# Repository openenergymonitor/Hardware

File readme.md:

## OpenEnergyMonitor Hardware

OpenEnergyMonitor hardware is open source hardware. This github repository hosts all the Eagle schematic and board files for the hardware units in addition to images for quick access.

**Update: most hardware designs have now been moved to dedicated repos, see individual folders**

### EmonTx

- [emonTx SMT V3](emonTxV3) - Latest generation of the emonTx Arduino compatible low power wireless energy monitoring node
- [emonTx Through-hole V2](emonTxV2) - A low-power wireless energy-monitoring node - Arduino compatible

### EmonTx Shield

- [emonTx Shield SMT](emontx-shield-smt) - An Arduino compatible energy monitoring shield
- [emonTx Shield Through-hole](emontx-shield-v1) - A wireless energy monitoring Arduino compatible shield

### EmonTH

- [emonTH](emonTH) - Temperature and humidity monitoring node

### EmonGLCD

- [emonGLCD](emonGLCD_V1) - Wireless open-source graphical LCD display unit - Arduino compatible

### RF12Pi Adapter Board

- [RF12Pi Adapter Board](RFM2Pi/readme.md)

### Development

- [12 Input Pulse Counter](12-input-pulse-counter) - Design in development for a 12-input puse counter for interfacing with 12 utility meters. 12 Input Pulse counter development notes and documentation can be found on the main OpenEnergyMonitor site [here](http://openenergymonitor.org/emon/buildingblocks/12-input-pulse-counting)

- [In-line energy monitor + Relay unit](relay-unit/readme.md)

### Open Hardware

Hardware designs (schematics and CAD) files are licensed under the [Creative Commons Attribution-ShareAlike 3.0 Unported License](http://creativecommons.org/licenses/by-sa/3.0/) and follow the terms of the [OSHW (Open-source hardware) Statement of Principles 1.0.](http://freedomdefined.org/OSHW)

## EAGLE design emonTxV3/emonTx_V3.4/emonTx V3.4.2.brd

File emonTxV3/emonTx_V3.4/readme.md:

## Moved to https://github.com/openenergymonitor/emontx3

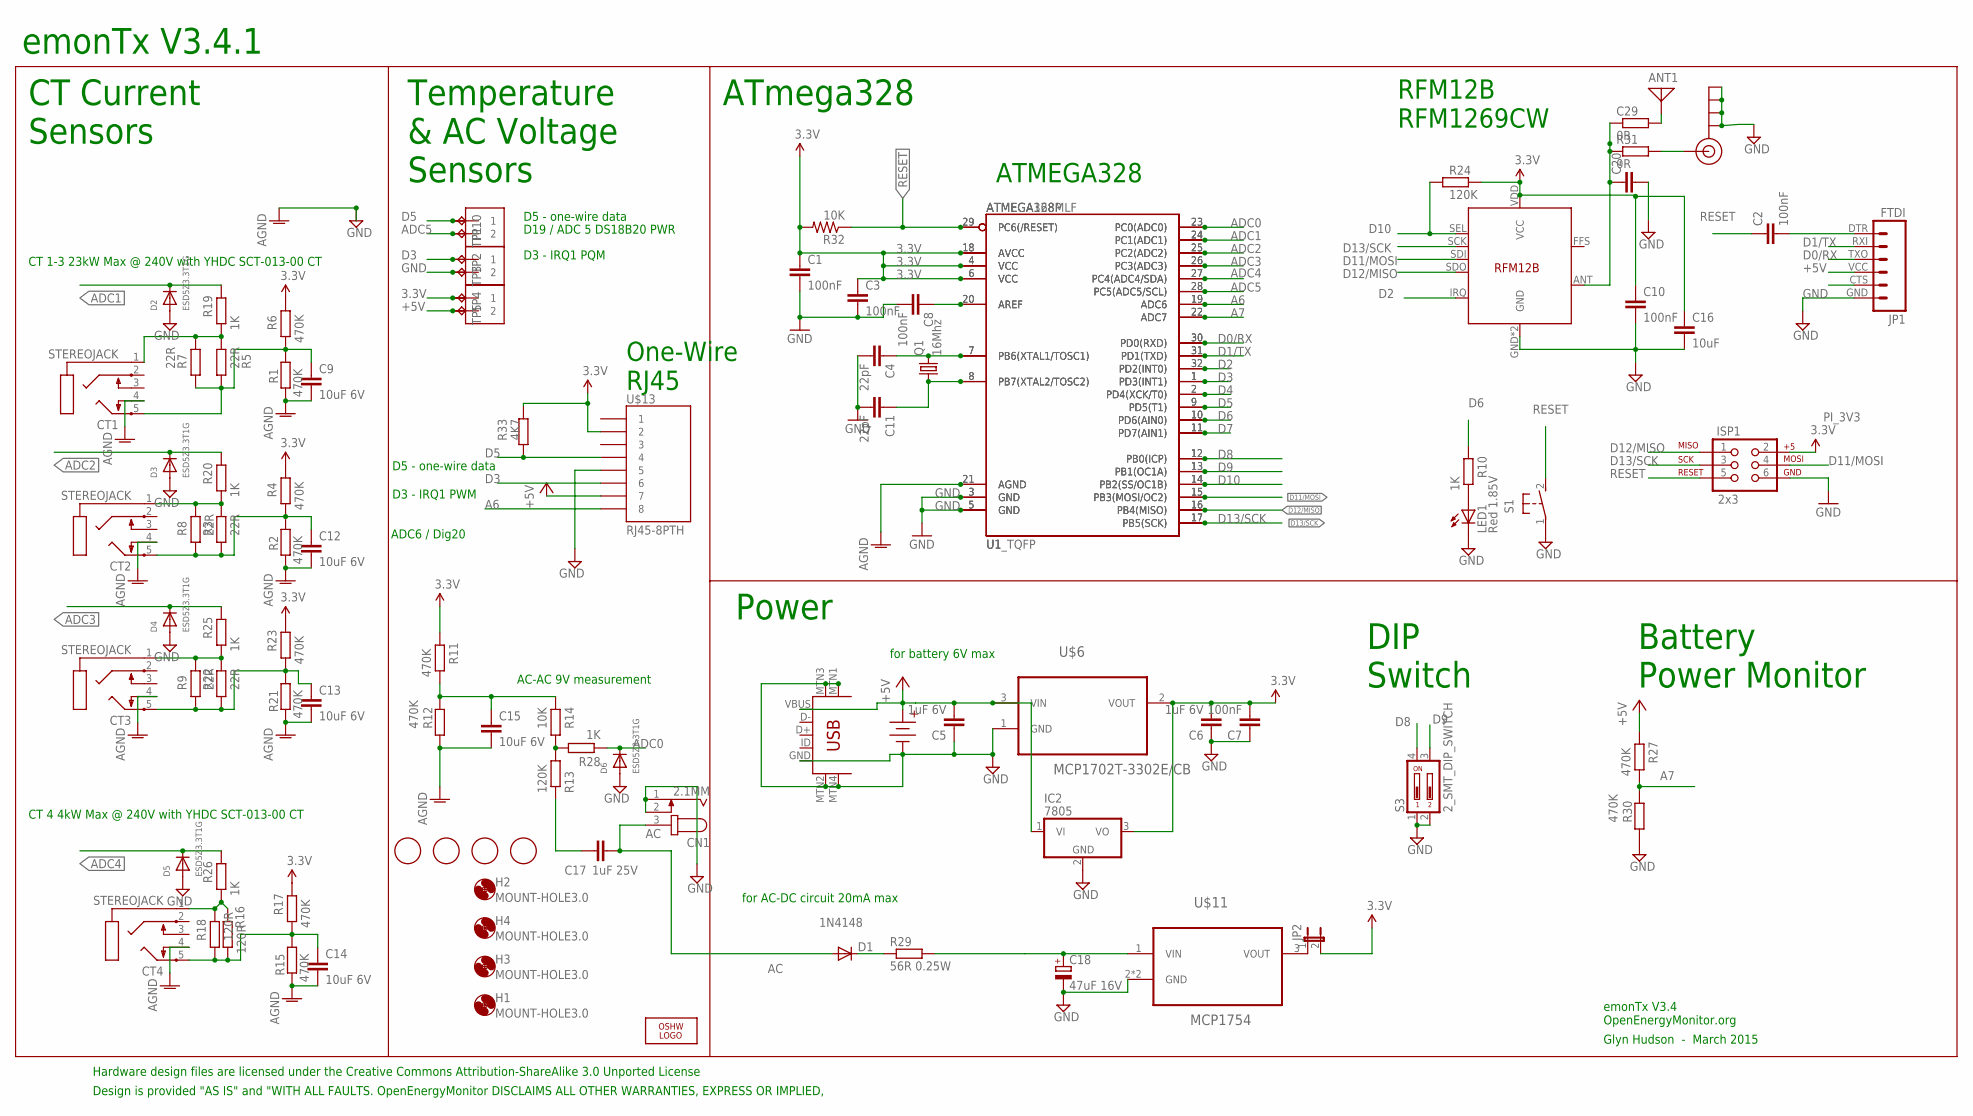
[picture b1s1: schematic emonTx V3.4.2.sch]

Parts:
ANT1: ANTENNA; PAD-01
C1, C2, C3, C7, C8, C10: 100nF; C0603
C4, C11: 22pF; C0603
C5, C6: 1uF 6V; C0603
C9, C12, C13, C14, C15: 10uF 6V; C0603
C16: 10uF; C0603
C17: 1uF 25V; C0603
C18: 47uF 16V; PANASONIC_D
C20: ant tune?; C0603
C29: 0R; R0603
CN1: 2.1MM; SPC4077
CT1, CT2, CT3, CT4: STEREOJACK; STX3100
D1: 1N4148; SOD-323
D2, D3, D4, D5, D6: ESD5Z3.3T1G; SOD-523
H1, H2, H3, H4: MOUNT-HOLE3.0; 3,0
IC2: 7805; TO220V
ISP1: 2x3; 2X3
J3, J5, J6: 1X2-3.5MM
J$1: SMA_EDGE; SMA-EDGE
JP1: FTDI; FTDI_BASIC
JP2: JUMPER-2PTH_LOCK; 1X02_LOCK
LED1: Red 1.85V; CHIP-LED0805
LOGO1: OSHW_LOGO_6MILX0200-NT; OSHW_6X200_NOTEXT
Q1: 16Mhz; HC49UP
R1, R2, R4, R6, R11, R12, R15, R17, R21, R23, R27, R30: 470K; R0603
R3, R5, R22: 22R; 0204/7
R7, R8, R9: 22R; R1206
R10, R19, R20, R25, R26, R28: 1K; R0603
R13, R24: 120K; R0603
R14, R32: 10K; R0603
R16: 120R; 0204/7
R18: 120R; R1206
R29: 56R 0.25W; R1206
R31: 0R; R0603
R33: 4K7; R0603
S1: 31-XX; B3F-31XX
S3: 2_SMT_DIP_SWITCH; DIP_SWITCH_SMT
TP1, TP2, TP3, TP4, TP5, TP10: TPPAD1-13; P1-13
U1: ATMEGA168MLF; MLF32
U1_TQFP: ATMEGA328P; TQFP32-08
U$1, U$4, U$5, U$7: FIDUCIAL; FIDUCIAL_1MM
U$3: 4.5V; AAA_PCB_HOLDER
U$6: MCP1702T-3302E/CB; SOT95P237X112-3N
U$10: USB-MINIB-5PIN; USB-MINIB-CISECO
U$11: MCP1754; SOT89
U$13: RJ45-8PTH; RJ45-8
U$14: RFM12B

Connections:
3.3V: C1.1, C3.1, C6.2, C7.2, C10.1, C16.1, IC2.3 (VO), ISP1.2, J6.1, JP2.2, R4.2, R6.2, R11.2, R17.2, R23.2, R24.2, R32.2, R33.1, TP4.TP, U1.4 (VCC), U1.6 (VCC), U1.18 (AVCC), U1_TQFP.4 (VCC), U1_TQFP.6 (VCC), U1_TQFP.18 (AVCC), U$6.2 (VOUT), U$13.2, U$14.VDD (VCC)
+5V: C5.2, IC2.1 (VI), J6.2, JP1.VCC (4), R27.2, TP5.TP, U$3.+, U$6.3 (VIN), U$10.VBUS, U$13.7
A6: U1.19 (ADC6), U1_TQFP.19 (ADC6), U$13.8
A7: R27.1, R30.2, U1.22 (ADC7), U1_TQFP.22 (ADC7)
AC: C17.2, CN1.3, D1.2 (A)
ADC0: D6.K (C), R28.1, U1.23 (PC0(ADC0)), U1_TQFP.23 (PC0(ADC0))
ADC1: D2.K (C), R19.2, U1.24 (PC1(ADC1)), U1_TQFP.24 (PC1(ADC1))
ADC2: D3.K (C), R20.2, U1.25 (PC2(ADC2)), U1_TQFP.25 (PC2(ADC2))
ADC3: D4.K (C), R25.2, U1.26 (PC3(ADC3)), U1_TQFP.26 (PC3(ADC3))
ADC4: D5.K (C), R26.2, U1.27 (PC4(ADC4/SDA)), U1_TQFP.27 (PC4(ADC4/SDA))
ADC5: J3.2, TP1.TP, U1.28 (PC5(ADC5/SCL)), U1_TQFP.28 (PC5(ADC5/SCL))
AGND: C9.2, C12.2, C13.2, C14.2, C15.2, CT1.4, CT2.4, CT3.4, CT4.4, R1.2, R2.2, R12.1, R15.2, R21.2, U1.21 (AGND), U1_TQFP.21 (AGND)
D0/RX: JP1.TXO (3), U1.30 (PD0(RXD)), U1_TQFP.30 (PD0(RXD))
D1/TX: JP1.RXI (2), U1.31 (PD1(TXD)), U1_TQFP.31 (PD1(TXD))
D2: U1.32 (PD2(INT0)), U1_TQFP.32 (PD2(INT0)), U$14.IRQ
D3: J5.1, TP2.TP, U1.1 (PD3(INT1)), U1_TQFP.1 (PD3(INT1)), U$13.6
D4: U1.2 (PD4(XCK/T0)), U1_TQFP.2 (PD4(XCK/T0))
D5: J3.1, R33.2, TP10.TP, U1.9 (PD5(T1)), U1_TQFP.9 (PD5(T1)), U$13.4
D6: R10.2, U1.10 (PD6(AIN0)), U1_TQFP.10 (PD6(AIN0))
D7: U1.11 (PD7(AIN1)), U1_TQFP.11 (PD7(AIN1))
D8: S3.4, U1.12 (PB0(ICP)), U1_TQFP.12 (PB0(ICP))
D9: S3.3, U1.13 (PB1(OC1A)), U1_TQFP.13 (PB1(OC1A))
D10: R24.1, U1.14 (PB2(SS/OC1B)), U1_TQFP.14 (PB2(SS/OC1B)), U$14.SEL
D11/MOSI: ISP1.4, U1.15 (PB3(MOSI/OC2)), U1_TQFP.15 (PB3(MOSI/OC2)), U$14.SDI
D12/MISO: ISP1.1, U1.16 (PB4(MISO)), U1_TQFP.16 (PB4(MISO)), U$14.SDO
D13/SCK: ISP1.3, U1.17 (PB5(SCK)), U1_TQFP.17 (PB5(SCK)), U$14.SCK
DIG1: C20.1, C29.1, R31.1, U$14.ANT
GND: C1.2, C3.2, C4.2, C5.1, C6.1, C7.1, C8.2, C10.2, C11.2, C16.2, C18.-, C20.2, CN1.1, CN1.2, D2.A, D3.A, D4.A, D5.A, D6.A, IC2.2 (GND), ISP1.6, J5.2, J$1.GND@0 (GND), J$1.GND@1 (GND), J$1.GND@2 (GND), J$1.GND@3 (GND), JP1.GND (6), LED1.C, R30.1, S1.1, S3.1, S3.2, TP3.TP, U1.3 (GND), U1.5 (GND), U1_TQFP.3 (GND), U1_TQFP.5 (GND), U$3.-, U$6.1 (GND), U$10.GND, U$10.MTN1 (MTN2), U$10.MTN2 (MTN3), U$10.MTN3 (MTN1), U$10.MTN4, U$11.2 (GND), U$11.2.1 (GND), U$13.5, U$14.GND, U$14.P$12 (GND)
unnamed: C4.1, Q1.2, U1.7 (PB6(XTAL1/TOSC1)), U1_TQFP.7 (PB6(XTAL1/TOSC1))
unnamed: CT1.1, R5.2, R7.2, R19.1
unnamed: C13.1, CT3.5, R9.1, R21.1, R22.1, R23.1
unnamed: R13.2, R14.1, R28.2
unnamed: JP2.1, U$11.3 (VOUT)
unnamed: C18.+, R29.2, U$11.1 (VIN)
unnamed: C17.1, R13.1
unnamed: CT4.1, R16.2, R18.2, R26.1
unnamed: C11.1, Q1.1, U1.8 (PB7(XTAL2/TOSC2)), U1_TQFP.8 (PB7(XTAL2/TOSC2))
unnamed: CT2.1, R3.2, R8.2, R20.1
unnamed: ANT1.1, C29.2
unnamed: D1.1 (C), R29.1
unnamed: CT3.1, R9.2, R22.2, R25.1
unnamed: C8.1, U1.20 (AREF), U1_TQFP.20 (AREF)
unnamed: C2.2, JP1.DTR (1)
unnamed: J$1.SIG (SIGNAL), R31.2
unnamed: C12.1, CT2.5, R2.1, R3.1, R4.1, R8.1
unnamed: C15.1, R11.1, R12.2, R14.2
unnamed: C14.1, CT4.5, R15.1, R16.1, R17.1, R18.1
unnamed: C9.1, CT1.5, R1.1, R5.1, R6.1, R7.1
unnamed: LED1.A, R10.1
RESET: C2.1, ISP1.5, R32.1, S1.2 (S), U1.29 (PC6(/RESET)), U1_TQFP.29 (PC6(/RESET))

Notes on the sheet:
AC-AC 9V measurement
emonTx V3.4 OpenEnergyMonitor.org
Glyn Hudson - March 2015
CT 4 4kW Max @ 240V with YHDC SCT-013-00 CT
CT 1-3 23kW Max @ 240V with YHDC SCT-013-00 CT
for battery 6V max
for AC-DC circuit 20mA max
Power
ATmega328
CT Current Sensors
Temperature & AC Voltage Sensors
Design is provided "AS IS" and "WITH ALL FAULTS. OpenEnergyMonitor DISCLAIMS ALL OTHER WARRANTIES, EXPRESS OR IMPLIED,
Hardware design files are licensed under the Creative Commons Attribution-ShareAlike 3.0 Unported License
emonTx V3.4.1
D19 / ADC 5 DS18B20 PWR
D5 - one-wire data
D3 - IRQ1 PQM
ATMEGA328
RFM12B RFM1269CW
One-Wire RJ45
D3 - IRQ1 PWM
ADC6 / Dig20
DIP Switch
Battery Power Monitor

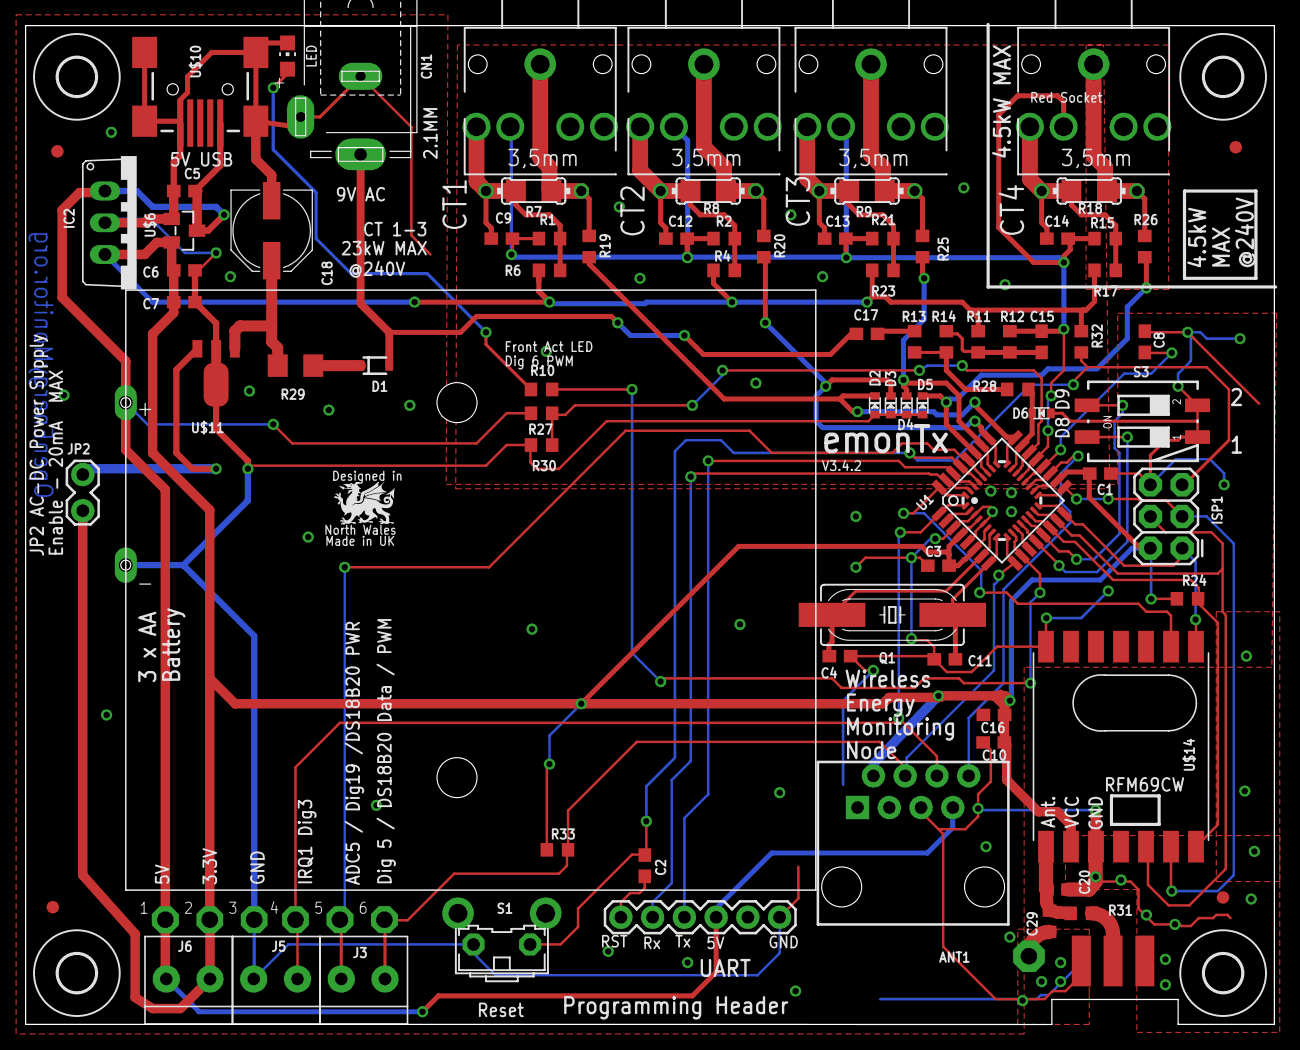
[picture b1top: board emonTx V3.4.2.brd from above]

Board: 2 copper layers, 99.9 x 79.9 mm, 100 parts (1 on the bottom side), 50 nets.

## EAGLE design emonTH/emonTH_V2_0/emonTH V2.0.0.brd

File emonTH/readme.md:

## Moved tp:

## emonTH V1:

https://github.com/openenergymonitor/emonTH

## emonTH v2:

https://github.com/openenergymonitor/emonth2

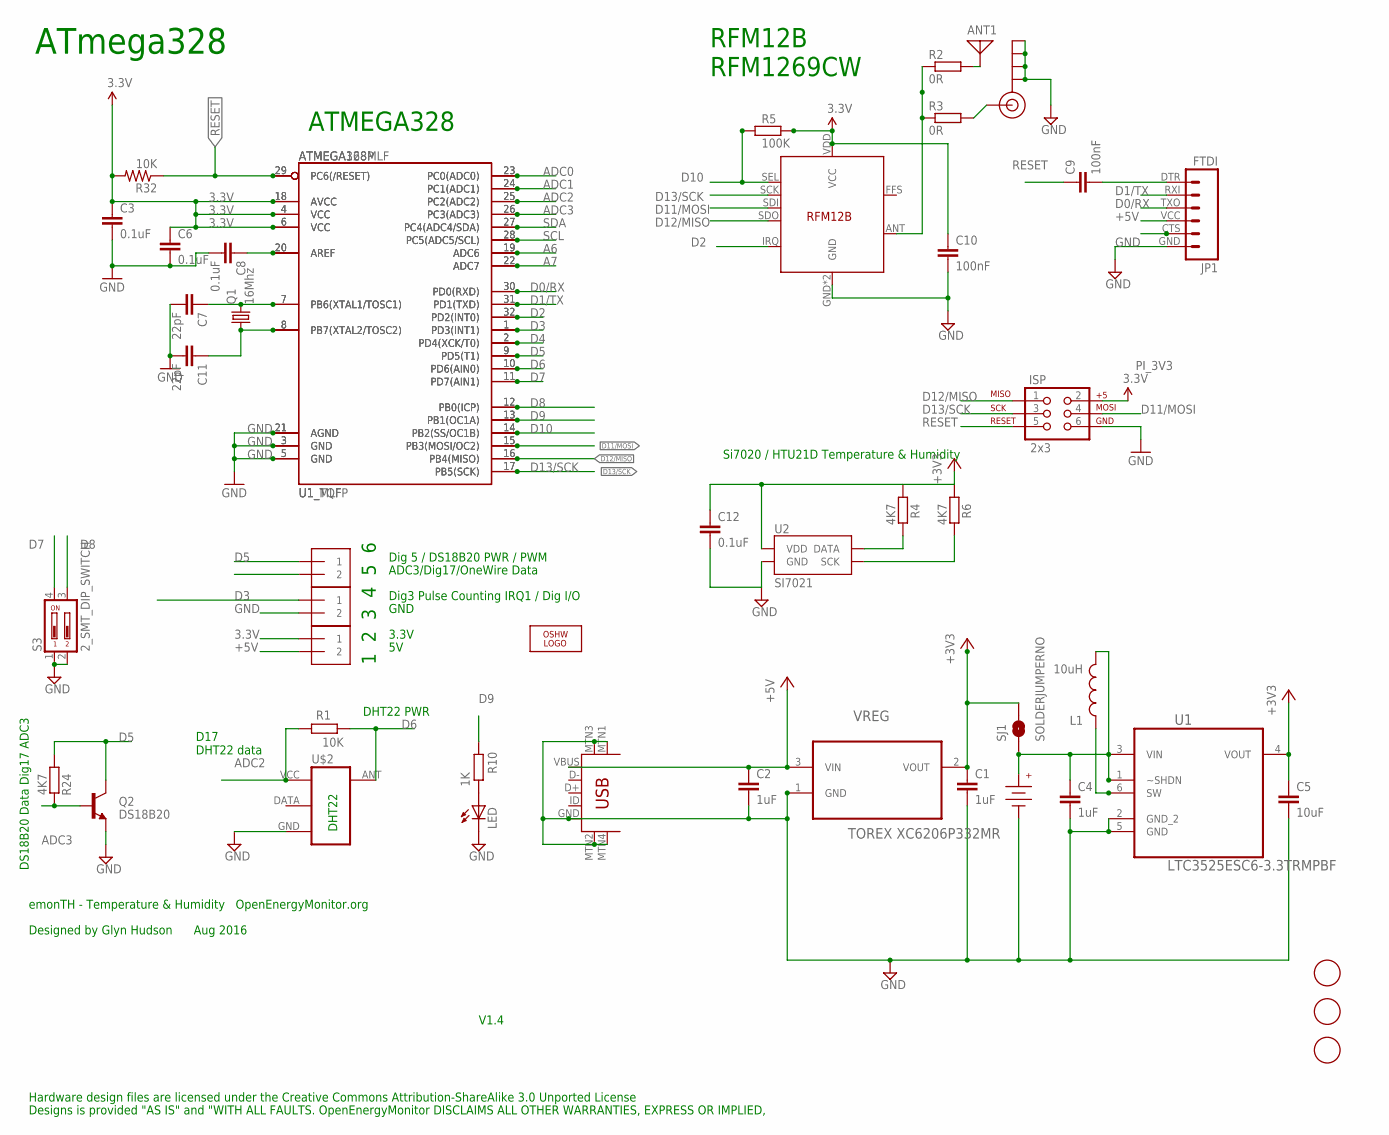
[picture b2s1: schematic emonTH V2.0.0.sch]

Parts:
ANT1: ANTENNA; PAD-01
C1, C2, C4: 1uF; C0603
C3, C6, C8, C12: 0.1uF; C0603
C5: 10uF; C0603
C7, C11: 22pF; C0603
C9, C10: 100nF; C0603
ISP: 2x3; 2X3
J1, J2, J3: 1X2-3.5MM
J$1: SMA_EDGE; SMA-EDGE
JP1: FTDI; FTDI_BASIC
L1: 10uH; 1210
LED: LEDCHIPLED-0603-TTW; CHIPLED-0603-TTW
LOGO2: OSHW_LOGO_10MILX0200-NT; OSHW_10X200_NOTEXT
Q1: 16Mhz; HC49UP
Q2: DS18B20; TO-92
R1, R32: 10K; R0603
R2, R3: 0R; R0603
R4, R6, R24: 4K7; R0603
R5: 100K; R0603
R10: 1K; R0603
RFM69CW: RFM12B
S3: 2_SMT_DIP_SWITCH; DIP_SWITCH_SMT
SJ1: SOLDERJUMPERNO; SJ_2S-NO
U1: LTC3525ESC6-3.3TRMPBF; SOT65P210X100-6N
U1_MLF: ATMEGA168MLF; MLF32
U1_TQFP: ATMEGA328P; TQFP32-08
U2: SI7021
U$1, U$6, U$7: FIDUCIAL; FIDUCIAL_1MM
U$2: RF-LINK_TX
U$3: 3V; AAA_PCB_HOLDER
U$5: USB-MINIB-5PIN; USB-MINIB-CISECO
VREG: TOREX XC6206P332MR; SOT95P237X112-3N

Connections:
3.3V: C1.1, C3.1, C5.1, C6.1, C10.1, C12.1, ISP.2, J3.1, R4.1, R5.2, R6.1, R32.2, RFM69CW.VDD (VCC), SJ1.2, U1.4 (VOUT), U1_MLF.4 (VCC), U1_MLF.6 (VCC), U1_MLF.18 (AVCC), U1_TQFP.4 (VCC), U1_TQFP.6 (VCC), U1_TQFP.18 (AVCC), U2.VDD, VREG.2 (VOUT)
+5V: C2.1, J3.2, JP1.VCC (4), U$5.VBUS, VREG.3 (VIN)
A6: U1_MLF.19 (ADC6), U1_TQFP.19 (ADC6)
A7: U1_MLF.22 (ADC7), U1_TQFP.22 (ADC7)
ADC0: U1_MLF.23 (PC0(ADC0)), U1_TQFP.23 (PC0(ADC0))
ADC1: C4.1, L1.2, SJ1.1, U1.1 (~SHDN), U1.3 (VIN), U1_MLF.24 (PC1(ADC1)), U1_TQFP.24 (PC1(ADC1)), U$3.+
ADC2: R1.2, U1_MLF.25 (PC2(ADC2)), U1_TQFP.25 (PC2(ADC2)), U$2.VCC (+5V)
ADC3: J1.2, Q2.2 (B), R24.2, U1_MLF.26 (PC3(ADC3)), U1_TQFP.26 (PC3(ADC3))
D0/RX: JP1.TXO (3), U1_MLF.30 (PD0(RXD)), U1_TQFP.30 (PD0(RXD))
D1/TX: JP1.RXI (2), U1_MLF.31 (PD1(TXD)), U1_TQFP.31 (PD1(TXD))
D2: RFM69CW.IRQ, U1_MLF.32 (PD2(INT0)), U1_TQFP.32 (PD2(INT0))
D3: J2.1, U1_MLF.1 (PD3(INT1)), U1_TQFP.1 (PD3(INT1))
D4: U1_MLF.2 (PD4(XCK/T0)), U1_TQFP.2 (PD4(XCK/T0))
D5: J1.1, Q2.3 (C), R24.1, U1_MLF.9 (PD5(T1)), U1_TQFP.9 (PD5(T1))
D6: R1.1, U1_MLF.10 (PD6(AIN0)), U1_TQFP.10 (PD6(AIN0)), U$2.ANT
D7: S3.4, U1_MLF.11 (PD7(AIN1)), U1_TQFP.11 (PD7(AIN1))
D8: S3.3, U1_MLF.12 (PB0(ICP)), U1_TQFP.12 (PB0(ICP))
D9: R10.2, U1_MLF.13 (PB1(OC1A)), U1_TQFP.13 (PB1(OC1A))
D10: R5.1, RFM69CW.SEL, U1_MLF.14 (PB2(SS/OC1B)), U1_TQFP.14 (PB2(SS/OC1B))
D11/MOSI: ISP.4, RFM69CW.SDI, U1_MLF.15 (PB3(MOSI/OC2)), U1_TQFP.15 (PB3(MOSI/OC2))
D12/MISO: ISP.1, RFM69CW.SDO, U1_MLF.16 (PB4(MISO)), U1_TQFP.16 (PB4(MISO))
D13/SCK: ISP.3, RFM69CW.SCK, U1_MLF.17 (PB5(SCK)), U1_TQFP.17 (PB5(SCK))
DIG1: R2.1, R3.1, RFM69CW.ANT
GND: C1.2, C2.2, C3.2, C4.2, C5.2, C6.2, C7.2, C8.2, C10.2, C11.2, C12.2, ISP.6, J2.2, J$1.GND@0 (GND), J$1.GND@1 (GND), J$1.GND@2 (GND), J$1.GND@3 (GND), JP1.GND (6), LED.C, Q2.1 (E), RFM69CW.GND, RFM69CW.P$12 (GND), S3.1, S3.2, U1.2 (GND_2), U1.5 (GND), U1_MLF.3 (GND), U1_MLF.5 (GND), U1_MLF.21 (AGND), U1_TQFP.3 (GND), U1_TQFP.5 (GND), U1_TQFP.21 (AGND), U2.GND, U$2.GND, U$3.-, U$5.GND, U$5.MTN1 (MTN2), U$5.MTN2 (MTN3), U$5.MTN3 (MTN1), U$5.MTN4, VREG.1 (GND)
unnamed: LED.A, R10.1
unnamed: C7.1, Q1.2, U1_MLF.7 (PB6(XTAL1/TOSC1)), U1_TQFP.7 (PB6(XTAL1/TOSC1))
unnamed: L1.1, U1.6 (SW)
unnamed: C11.1, Q1.1, U1_MLF.8 (PB7(XTAL2/TOSC2)), U1_TQFP.8 (PB7(XTAL2/TOSC2))
unnamed: ANT1.1, R2.2
unnamed: C8.1, U1_MLF.20 (AREF), U1_TQFP.20 (AREF)
unnamed: C9.2, JP1.DTR (1)
unnamed: J$1.SIG (SIGNAL), R3.2
RESET: C9.1, ISP.5, R32.1, U1_MLF.29 (PC6(/RESET)), U1_TQFP.29 (PC6(/RESET))
SCL: R6.2, U1_MLF.28 (PC5(ADC5/SCL)), U1_TQFP.28 (PC5(ADC5/SCL)), U2.SCK
SDA: R4.2, U1_MLF.27 (PC4(ADC4/SDA)), U1_TQFP.27 (PC4(ADC4/SDA)), U2.DATA

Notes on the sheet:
emonTH - Temperature & Humidity OpenEnergyMonitor.org
Designed by Glyn Hudson Aug 2016
V1.4
DS18B20 Data Dig17 ADC3
ADC3/Dig17/OneWire Data
Dig 5 / DS18B20 PWR / PWM
Dig3 Pulse Counting IRQ1 / Dig I/O
GND
3.3V
DHT22
1 2 3 4 5 6
Hardware design files are licensed under the Creative Commons Attribution-ShareAlike 3.0 Unported License
Designs is provided "AS IS" and "WITH ALL FAULTS. OpenEnergyMonitor DISCLAIMS ALL OTHER WARRANTIES, EXPRESS OR IMPLIED,
ATmega328
ATMEGA328
RFM12B RFM1269CW
D17 DHT22 data
Si7020 / HTU21D Temperature & Humidity
DHT22 PWR

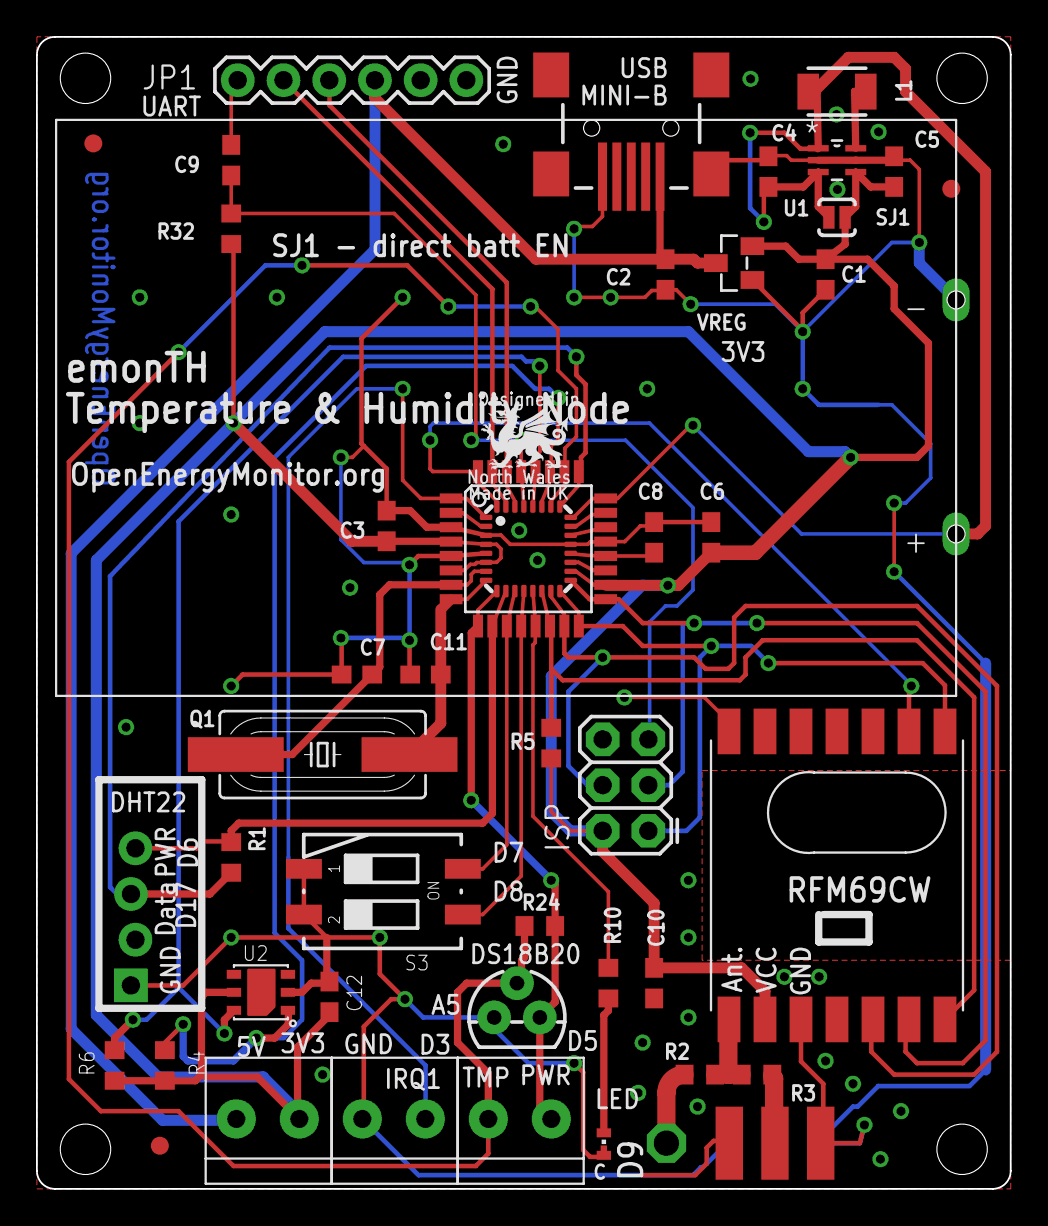
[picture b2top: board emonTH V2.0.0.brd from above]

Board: 2 copper layers, 54.1 x 64.0 mm, 47 parts (1 on the bottom side), 35 nets.

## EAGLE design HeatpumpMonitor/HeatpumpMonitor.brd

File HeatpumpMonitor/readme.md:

## Moved to: https://github.com/openenergymonitor/HeatpumpMonitor

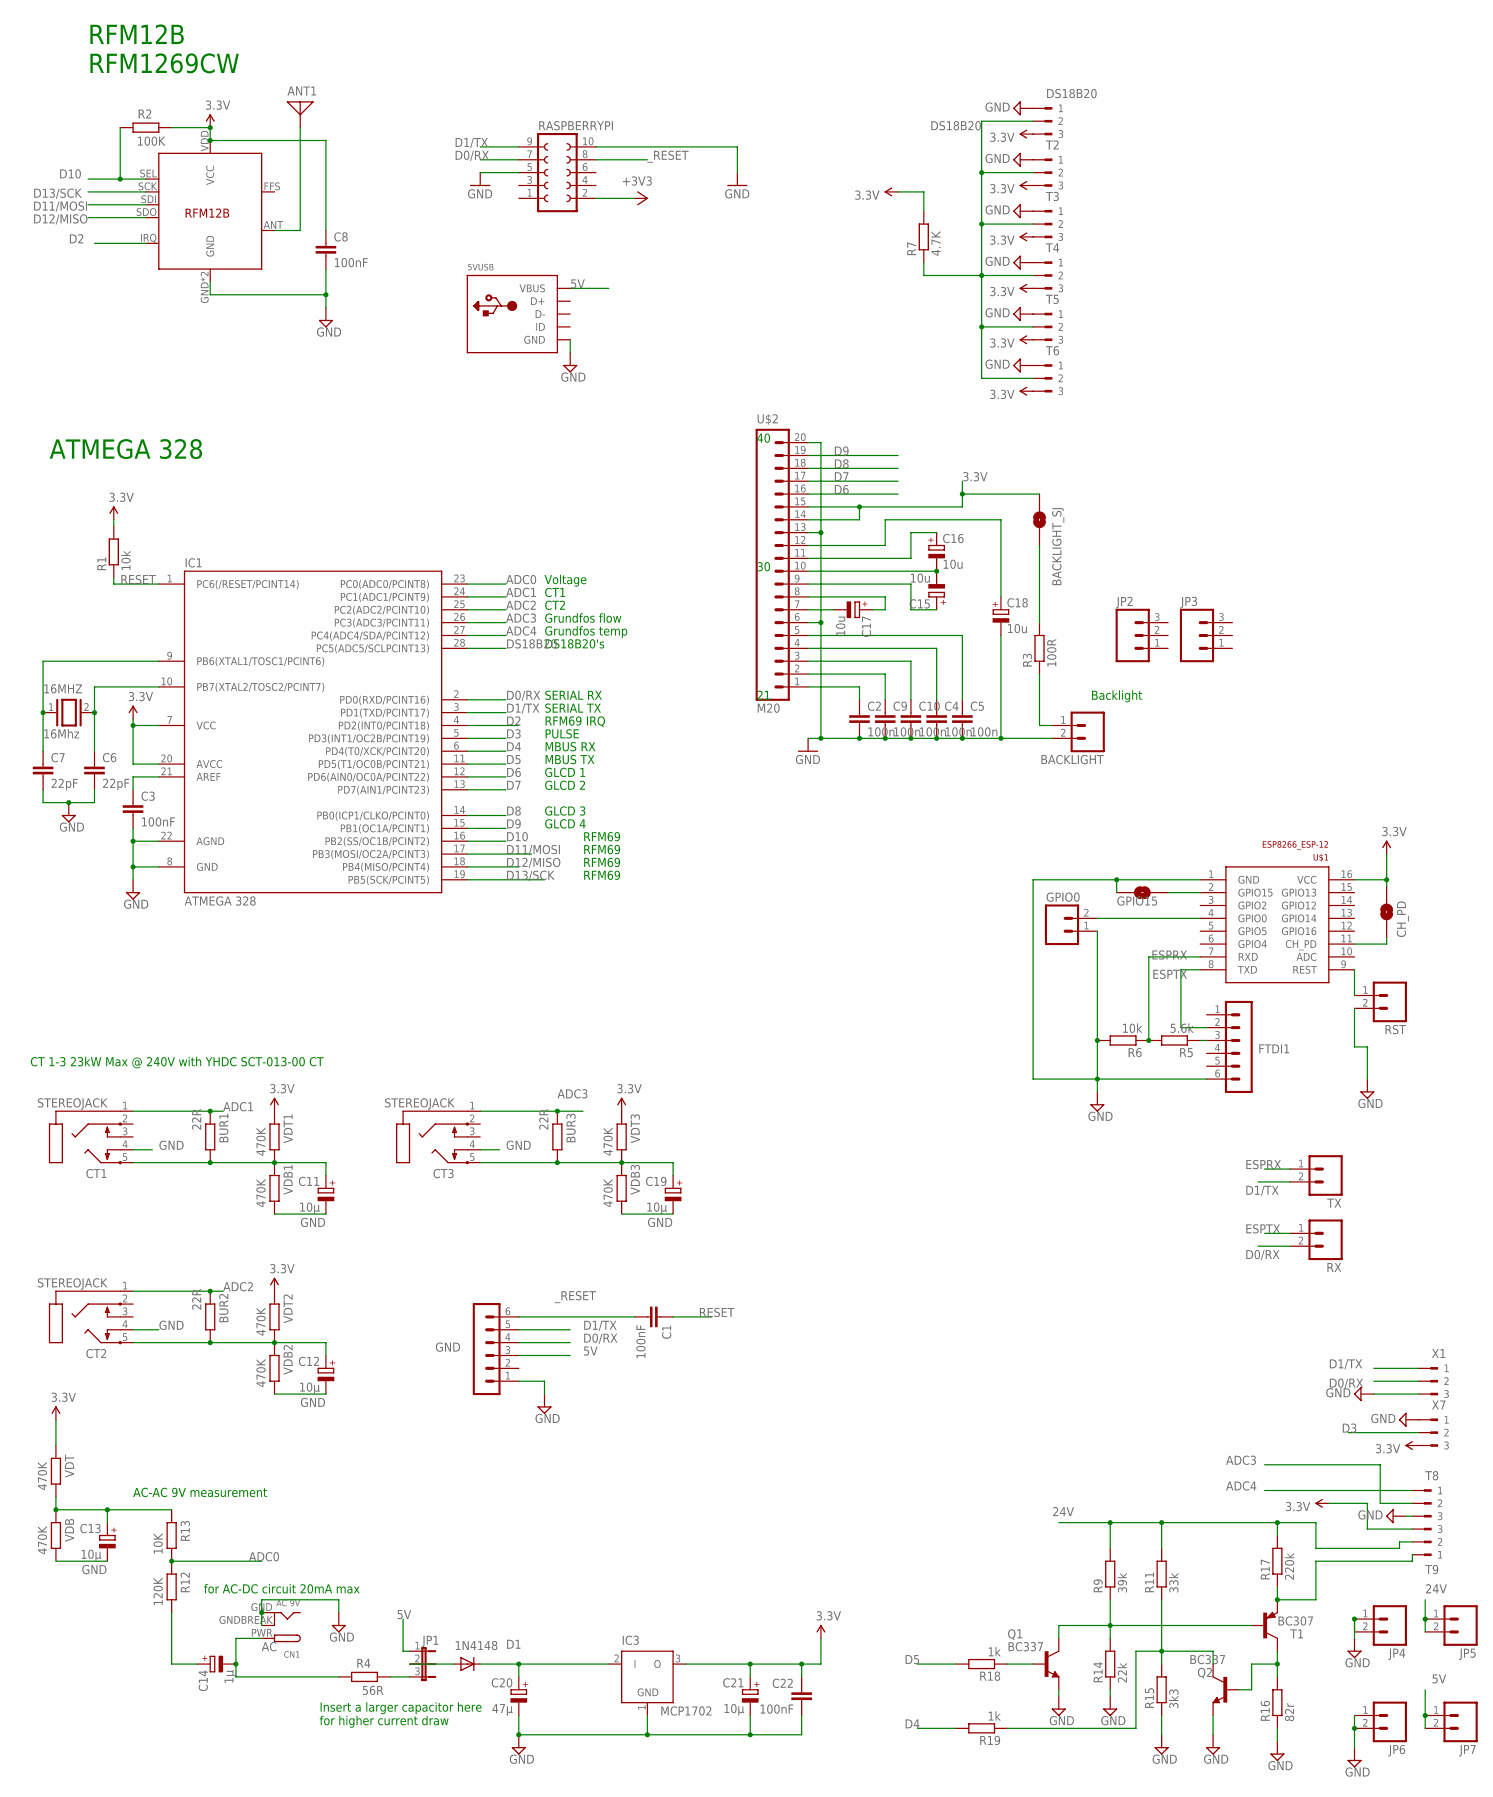
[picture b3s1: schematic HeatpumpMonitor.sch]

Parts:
5VUSB: USBMOLEX; USB-MINIB-THM-MOLEX
16MHZ: 16Mhz; QS
ANT1: ANTENNA; PAD-01
BACKLIGHT: M02PTH; 1X02
BACKLIGHT_SJ: SOLDERJUMPERNO; SJ_2S-NO
BUR1, BUR2, BUR3: 22R; 0204/7
C1, C3, C8, C22: 100nF; C025-024X044
C2, C4, C5, C9, C10: 100n; C2.5-2
C6, C7: 22pF; C2.5-2
C11, C12, C13, C19, C21: 10µ; E1,8-4
C14: 1µ; E1,8-4
C15, C16, C17, C18: 10u; E1,8-4
C20: 47µ; E1,8-4
CH_PD: SOLDERJUMPERNO; SJ_2S-NO
CN1: AC 9V; DCJACK_2MM_PTH
CT1, CT2, CT3: STEREOJACK; STX3100
D1: 1N4148; DIODE-1N4148
DS18B20: 180-3
FTDI1: FTDI; MA06-1
GND: FTDI; MA06-1
GPIO0: M02PTH; 1X02
GPIO15: SOLDERJUMPERNO; SJ_2S-NO
IC1: ATMEGA 328; DIL28-3
IC3: MCP1702; TO92
JP1: JP2E; JP2
JP2, JP3: M03PTH; 1X03
JP4, JP5, JP6, JP7: M02PTH; 1X02
Q1, Q2: BC337; TO92
R1, R6: 10k; 0204/7
R2: 100K; 0204/7
R3: 100R; 0204/7
R4: 56R; 0204/7
R5: 5.6k; 0204/7
R7: 4.7K; 0204/7
R9: 39k; 0204/7
R11: 33k; 0204/7
R12: 120K; 0204/7
R13: 10K; 0204/7
R14: 22k; 0204/7
R15: 3k3; 0204/7
R16: 82r; 0204/7
R17: 220k; 0204/7
R18, R19: 1k; 0204/7
RASPBERRYPI: FE05-2
RST: M02PTH; 1X02
RX: M02PTH; 1X02
T1: BC307; TO92
T2, T3, T4, T5, T6, T8, T9: 180-3
TX: M02PTH; 1X02
U$1: ESP8266_ESP-12; ESP8266-ESP12
U$2: M20; 1X20
U$14: RFM12B
VDB, VDB1, VDB2, VDB3: 470K; 0204/7
VDT, VDT1, VDT2, VDT3: 470K; 0204/7
X1, X7: 180-3

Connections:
3.3V: BACKLIGHT_SJ.1, C8.1, C21.+, C22.1, CH_PD.2, DS18B20.3, IC1.7 (VCC), IC1.20 (AVCC), IC3.3 (O), R1.2, R2.1, R7.2, RASPBERRYPI.2, T2.3, T3.3, T4.3, T5.3, T6.3, T9.3, U$1.16 (VCC), U$2.14, U$2.15, U$14.VDD (VCC), VDT.2, VDT1.2, VDT2.2, VDT3.2, X7.3
5V: 5VUSB.VBUS, GND.3, JP1.1, JP7.1, JP7.2
24V: JP5.1, JP5.2, R9.2, R11.2, R17.2, T9.2
AC: C14.-, CN1.PWR, R4.2
ADC0: IC1.23 (PC0(ADC0/PCINT8)), R12.2, R13.1
ADC1: BUR1.2, CT1.1, IC1.24 (PC1(ADC1/PCINT9))
ADC2: BUR2.2, CT2.1, IC1.25 (PC2(ADC2/PCINT10))
ADC3: BUR3.2, CT3.1, IC1.26 (PC3(ADC3/PCINT11)), T8.2
ADC4: IC1.27 (PC4(ADC4/SDA/PCINT12)), T8.1
D0/RX: GND.4, IC1.2 (PD0(RXD/PCINT16)), RASPBERRYPI.7, RX.2, X1.2
D1/TX: GND.5, IC1.3 (PD1(TXD/PCINT17)), RASPBERRYPI.9, TX.2, X1.1
D2: IC1.4 (PD2(INT0/PCINT18)), U$14.IRQ
D3: IC1.5 (PD3(INT1/OC2B/PCINT19)), X7.2
D4: IC1.6 (PD4(T0/XCK/PCINT20)), R19.2
D5: IC1.11 (PD5(T1/OC0B/PCINT21)), R18.2
D6: IC1.12 (PD6(AIN0/OC0A/PCINT22)), U$2.16
D7: IC1.13 (PD7(AIN1/PCINT23)), U$2.17
D8: IC1.14 (PB0(ICP1/CLKO/PCINT0)), U$2.18
D9: IC1.15 (PB1(OC1A/PCINT1)), U$2.19
D10: IC1.16 (PB2(SS/OC1B/PCINT2)), R2.2, U$14.SEL
D11/MOSI: IC1.17 (PB3(MOSI/OC2A/PCINT3)), U$14.SDI
D12/MISO: IC1.18 (PB4(MISO/PCINT4)), U$14.SDO
D13/SCK: IC1.19 (PB5(SCK/PCINT5)), U$14.SCK
DIG1: ANT1.1, U$14.ANT
DS18B20: DS18B20.2, IC1.28 (PC5(ADC5/SCLPCINT13)), R7.1, T2.2, T3.2, T4.2, T5.2, T6.2
ESPRX: R5.2, R6.1, TX.1, U$1.7 (RXD)
ESPTX: FTDI1.2, RX.1, U$1.8 (TXD)
GND: 5VUSB.GND, BACKLIGHT.2, C2.2, C3.2, C4.2, C5.2, C6.2, C7.2, C8.2, C9.2, C10.2, C11.-, C12.-, C13.-, C18.-, C19.-, C20.-, C21.-, C22.2, CN1.GND, CN1.GNDBREAK, CT1.4, CT2.4, CT3.4, DS18B20.1, FTDI1.6, GND.1, GPIO0.1, GPIO15.2, IC1.8 (GND), IC1.22 (AGND), IC3.1 (GND), JP4.1, JP4.2, JP6.1, JP6.2, Q1.1 (E), Q2.1 (E), R6.2, R14.1, R15.1, R16.1, RASPBERRYPI.5, RASPBERRYPI.10, RST.2, T2.1, T3.1, T4.1, T5.1, T6.1, T8.3, U$1.1 (GND), U$2.6, U$2.13, U$2.20, U$14.GND, U$14.P$12 (GND), VDB.1, VDB1.1, VDB2.1, VDB3.1, X1.3, X7.1
IRQ: BACKLIGHT_SJ.2, R3.2
unnamed: 16MHZ.2, C6.1, IC1.10 (PB7(XTAL2/TOSC2/PCINT7))
unnamed: BUR2.1, C12.+, CT2.5, VDB2.2, VDT2.1
unnamed: C2.1, U$2.1
unnamed: C9.1, U$2.2
unnamed: C10.1, U$2.3
unnamed: C4.1, U$2.4
unnamed: C14.+, R12.1
unnamed: BUR3.1, C19.+, CT3.5, VDB3.2, VDT3.1
unnamed: C5.1, U$2.5
unnamed: C15.-, C16.-, U$2.10
unnamed: C20.+, D1.C, IC3.2 (I)
unnamed: 16MHZ.1, C7.1, IC1.9 (PB6(XTAL1/TOSC1/PCINT6))
unnamed: R17.1, T1.1 (E), T9.1
unnamed: JP1.3, R4.1
unnamed: Q2.2 (B), R16.2, T1.3 (C)
unnamed: BACKLIGHT.1, R3.1
unnamed: Q1.3 (C), R9.1, R14.2, T1.2 (B)
unnamed: C3.1, IC1.21 (AREF)
unnamed: C16.+, U$2.11
unnamed: Q2.3 (C), R11.1, R15.2, R19.1
unnamed: C15.+, U$2.9
unnamed: C17.-, U$2.7
unnamed: D1.A, JP1.2
unnamed: Q1.2 (B), R18.1
unnamed: GPIO15.1, U$1.2 (GPIO15)
unnamed: C17.+, U$2.8
unnamed: C18.+, U$2.12
unnamed: GPIO0.2, U$1.4 (GPIO0)
unnamed: C13.+, R13.2, VDB.2, VDT.1
unnamed: FTDI1.3, R5.1
unnamed: BUR1.1, C11.+, CT1.5, VDB1.2, VDT1.1
unnamed: CH_PD.1, U$1.11 (CH_PD)
unnamed: RST.1, U$1.9 (REST)
RESET: C1.1, IC1.1 (PC6(/RESET/PCINT14)), R1.1
_RESET: C1.2, GND.6, RASPBERRYPI.8

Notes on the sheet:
ATMEGA 328
RFM12B RFM1269CW
CT 1-3 23kW Max @ 240V with YHDC SCT-013-00 CT
AC-AC 9V measurement
for AC-DC circuit 20mA max
Backlight
Voltage
CT1
CT2
SERIAL RX
SERIAL TX
RFM69 IRQ
MBUS RX
MBUS TX
PULSE
Grundfos flow
Grundfos temp
DS18B20's
GLCD 1
GLCD 2
GLCD 3
GLCD 4
RFM69
Insert a larger capacitor here for higher current draw

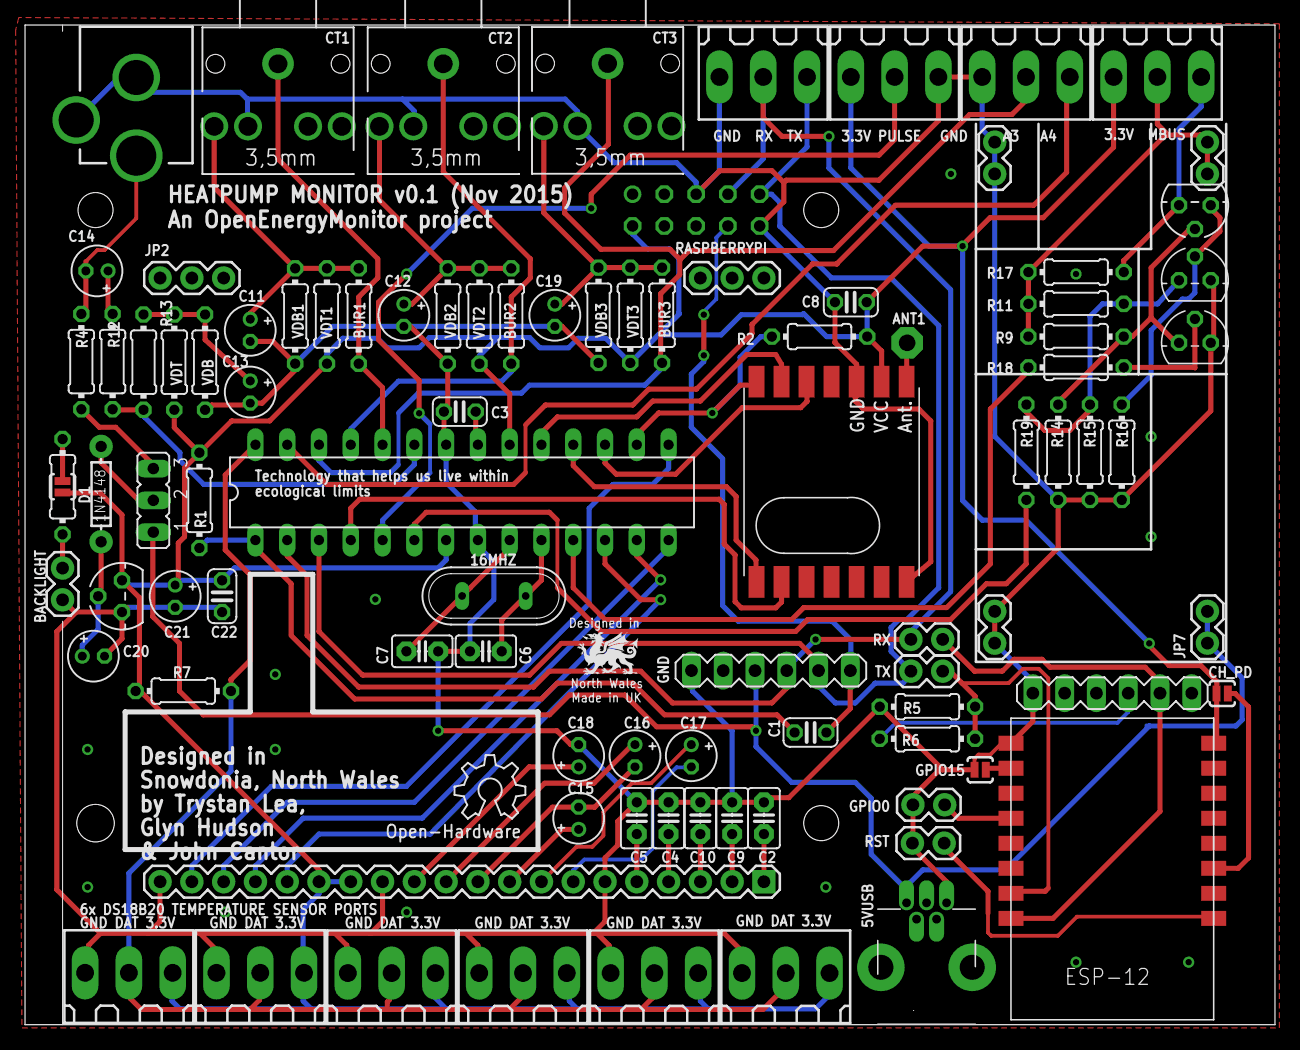
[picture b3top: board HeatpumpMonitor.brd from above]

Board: 2 copper layers, 99.9 x 79.9 mm, 95 parts (0 on the bottom side), 64 nets.

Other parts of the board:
LOGO1: OSHW_LOGO_6MILX0200-NT; OSHW_6X200_NOTEXT

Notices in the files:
parts and their libraries:
SparkFun-DigitalIC: Licensing: CC v3.0 Share-Alike You are welcome to use this library for commercial purposes.
SparkFun-Sensors: Licensing: Creative Commons ShareAlike 4.0 International - https://creativecommons.org/licenses/by-sa/4.0
